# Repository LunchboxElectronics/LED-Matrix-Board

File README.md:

# README #

Whoray a LEGO compatible LED Matrix Board!!

### What is this repository for? ###

This repo supplies instructions and source files to create and make derivatives of the LED Matrix Board kit. This kit is an array of 49 LEDs to be incorperated into existing brick projects. The board is compatible with LEGO sets.

* This repo contains:
Eagle Files 
Arduino code to run the display and animate a smile

### How do I get set up? ###

* Code is written in Arduino
* Board file and schematic are created in Eagle

### Licensing ###
LED Matrix Board is an open source hardware product and follows the open source hardware definition: www.oshwa.org/definition The Eagle Files are licensed CC-BY-SA: Lunchbox Electronics.

### Warrenty ###
Distributed as-is; no warranty given. Not suitable for people who might eat electronics.

### Who do I talk to? ###

* Created by Jason Brownstein @ Lunchbox Electronics 9/24/15
* Contact contact@lunchboxelectronics.com

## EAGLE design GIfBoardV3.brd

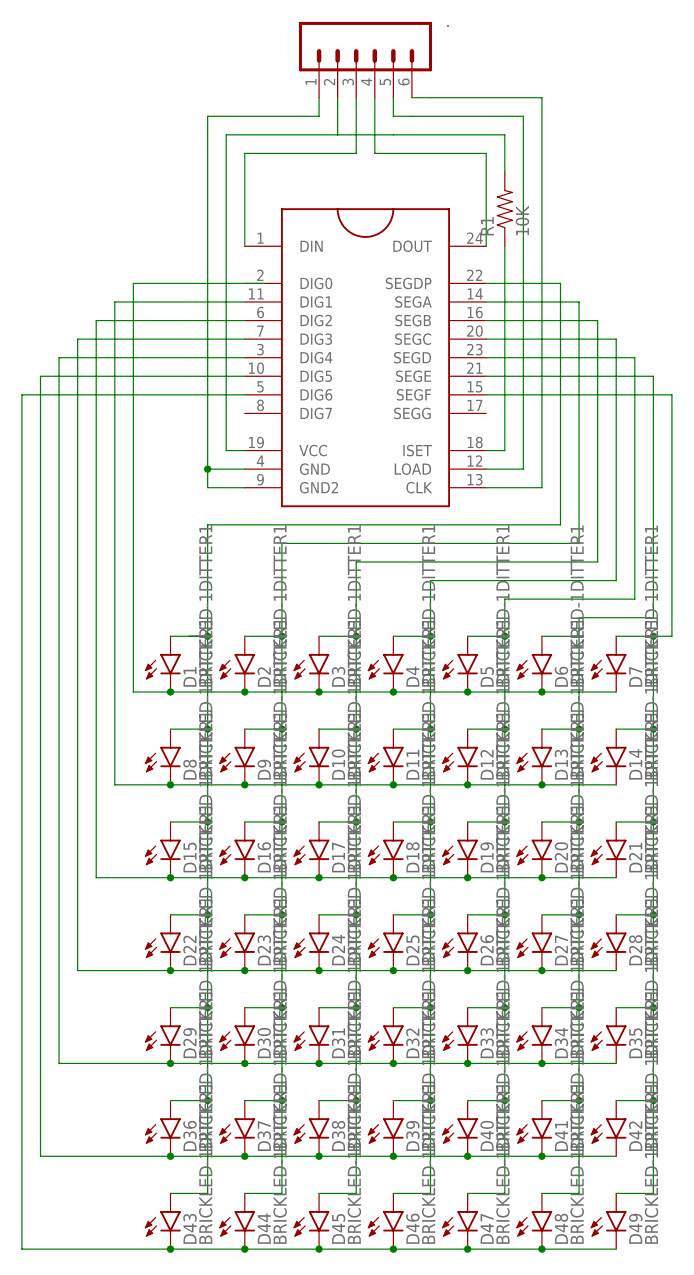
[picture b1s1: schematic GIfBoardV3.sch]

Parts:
.: M06NO_SILK_FEMALE_PTH; 1X06_NO_SILK
D1, D2, D3, D4, D5, D6, D7, D8, D9, D10, D11, D12, D13, D14, D15, D16, D17, D18, D19, D20, D21, D22, D23, D24, D25, D26, D27, D28, D29, D30, D31, D32, D33, D34, D35, D36, D37, D38, D39, D40, D41, D42, D43, D44, D45, D46, D47, D48, D49: BRICKLED-1DITTER1; BRICKLED-1DITTER
MAX7219: MAX7219DIP; DIL24
R1: 10K; AXIAL-0.3

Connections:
unnamed: ..4, MAX7219.24 (DOUT)
unnamed: ..5, MAX7219.12 (LOAD)
unnamed: ..3, MAX7219.1 (DIN)
unnamed: ..1, MAX7219.4 (GND), MAX7219.9 (GND2)
unnamed: D8.K (C), D9.K (C), D10.K (C), D11.K (C), D12.K (C), D13.K (C), D14.K (C), MAX7219.11 (DIG1)
unnamed: ..2, MAX7219.19 (VCC), R1.P$2 (2)
unnamed: ..6, MAX7219.13 (CLK)
unnamed: D1.A, D8.A, D15.A, D22.A, D29.A, D36.A, D43.A, MAX7219.22 (SEGDP)
unnamed: D1.K (C), D2.K (C), D3.K (C), D4.K (C), D5.K (C), D6.K (C), D7.K (C)
unnamed: D15.K (C), D16.K (C), D17.K (C), D18.K (C), D19.K (C), D20.K (C), D21.K (C), MAX7219.6 (DIG2)
unnamed: D2.A, D9.A, D16.A, D23.A, D30.A, D37.A, D44.A, MAX7219.14 (SEGA)
unnamed: D29.K (C), D30.K (C), D31.K (C), D32.K (C), D33.K (C), D34.K (C), D35.K (C), MAX7219.3 (DIG4)
unnamed: D36.K (C), D37.K (C), D38.K (C), D39.K (C), D40.K (C), D41.K (C), D42.K (C), MAX7219.10 (DIG5)
unnamed: D43.K (C), D44.K (C), D45.K (C), D46.K (C), D47.K (C), D48.K (C), D49.K (C), MAX7219.5 (DIG6)
unnamed: MAX7219.18 (ISET), R1.P$1 (1)
unnamed: D3.A, D10.A, D17.A, D24.A, D31.A, D38.A, D45.A, MAX7219.16 (SEGB)
unnamed: D5.A, D12.A, D19.A, D26.A, D33.A, D40.A, D47.A, MAX7219.23 (SEGD)
unnamed: D4.A, D11.A, D18.A, D25.A, D32.A, D39.A, D46.A, MAX7219.20 (SEGC)
unnamed: D6.A, D13.A, D20.A, D27.A, D34.A, D41.A, D48.A, MAX7219.21 (SEGE)
unnamed: D7.A, D14.A, D21.A, D28.A, D35.A, D42.A, D49.A, MAX7219.15 (SEGF)
unnamed: D22.K (C), D23.K (C), D24.K (C), D25.K (C), D26.K (C), D27.K (C), D28.K (C), MAX7219.7 (DIG3)

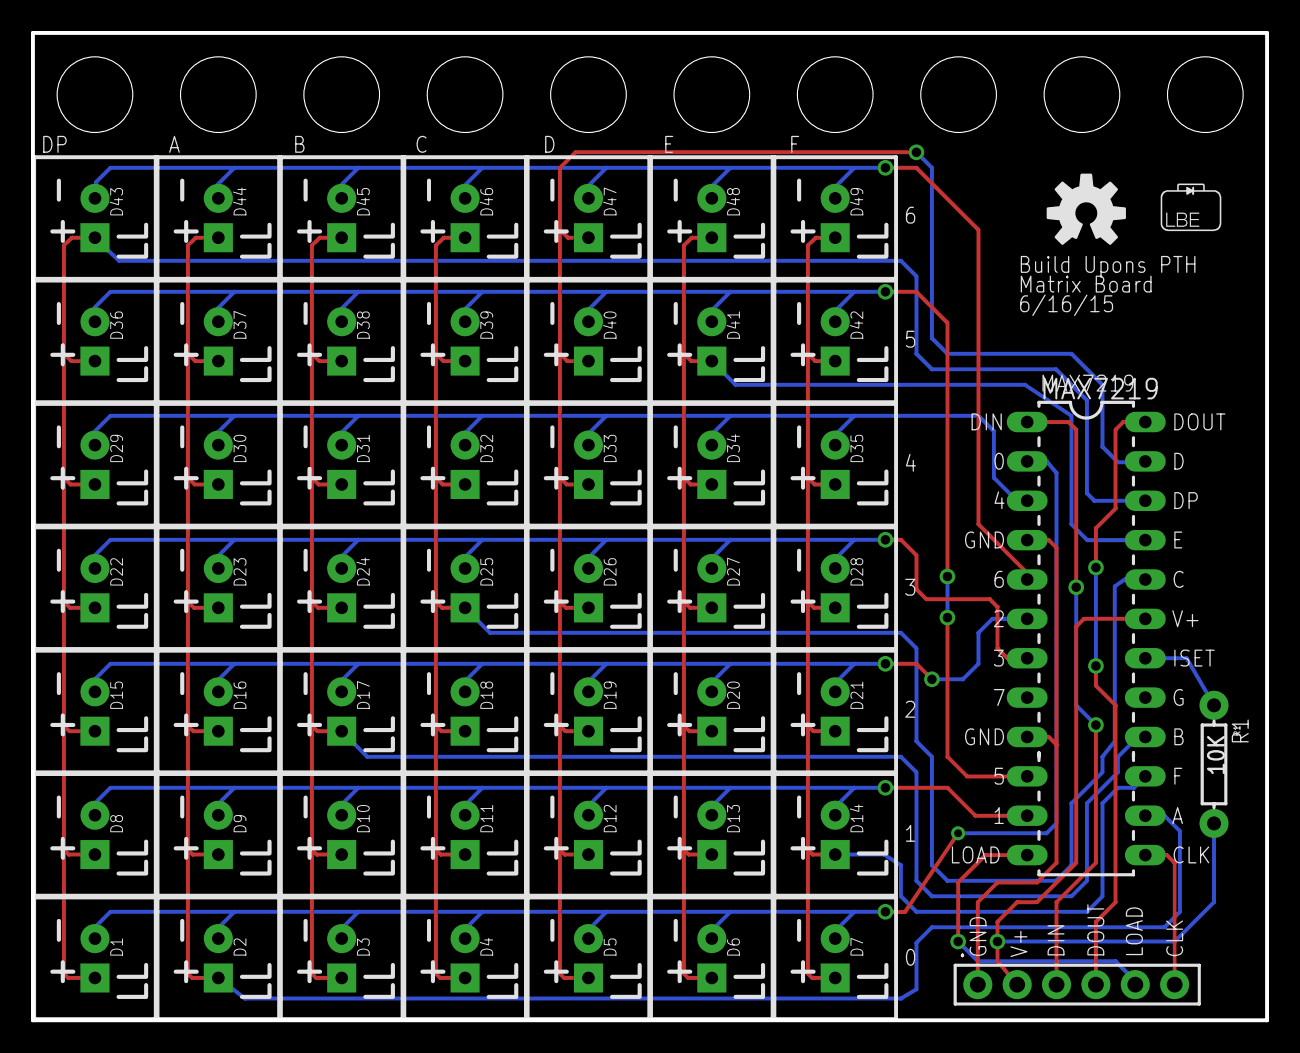
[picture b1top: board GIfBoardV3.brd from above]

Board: 2 copper layers, 79.6 x 63.7 mm, 54 parts (0 on the bottom side), 21 nets.

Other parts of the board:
U$2: OSHW-LOGO-M
U$3: LUNCHBOXELECTRONICS

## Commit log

2016-04-27 Adding files

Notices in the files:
parts and their libraries:
SparkFun-Connectors: Licensing: Creative Commons ShareAlike 4.0 International - https://creativecommons.org/licenses/by-sa/4.0
